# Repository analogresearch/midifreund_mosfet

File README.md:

# midifreund_mosfet

DC IN: 9..28 V 

Ansteuerung durch MIDI note 36 (C2) und eine Oktave dur hoch bis C3.
also:
36 38 40 41 43 45 47 48

MIDI channel und Programm werden binär über DIP Schalter gewählt.

MIDI: Ausnahme DIP Schalter 0000 = MIDI channel 16!

Programme:  
(0) note on schaltet ein, note off schaltet aus.

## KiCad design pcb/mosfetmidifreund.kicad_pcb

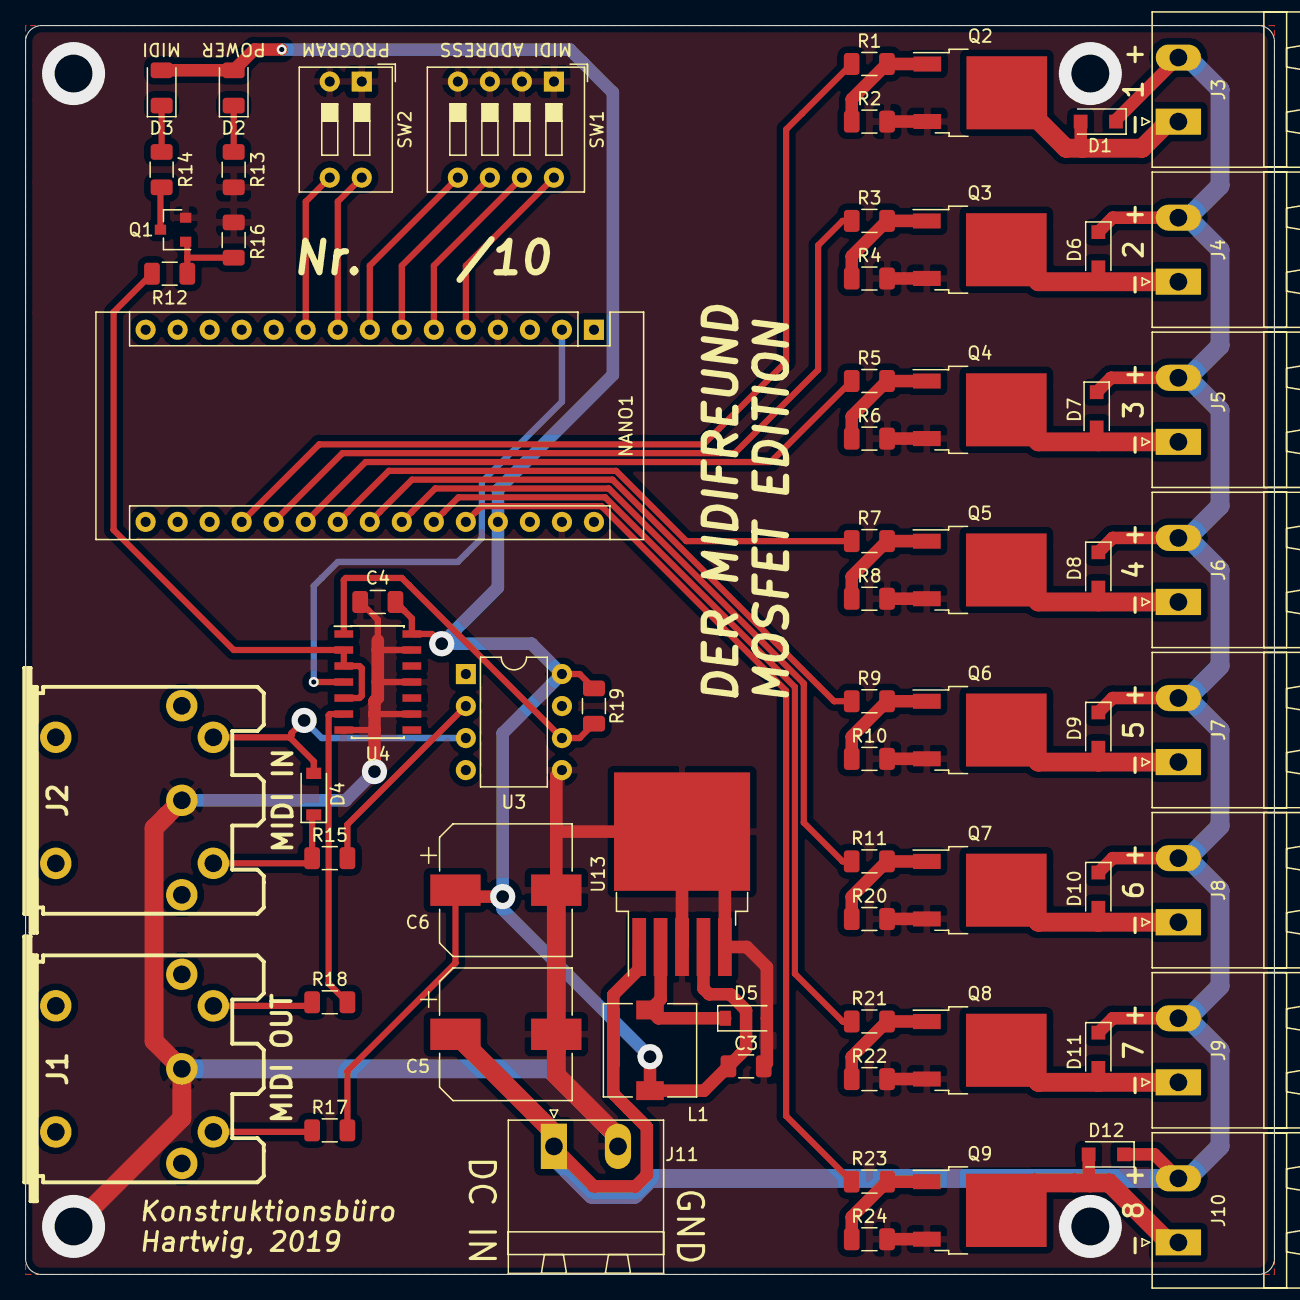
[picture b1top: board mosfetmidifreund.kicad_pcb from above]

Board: 2 copper layers, 99.1 x 99.1 mm, 67 parts (0 on the bottom side), 47 nets.

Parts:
C3, C4: 100n; C_1206_3216Metric
C5, C6: 330uF; CP_Elec_10x10
D1, D6, D7, D8, D9, D10, D11, D12: 1N4001; D_SOD-123F
D2: POWER; LED_1206_3216Metric
D3: MIDI; LED_1206_3216Metric
D4: 1N4148; D_SOD-123
D5: 1N5819; D_SOD-123
J1: MIDI OUT; MIDI_DIN5
J2: MIDI IN; MIDI_DIN5
J3, J4, J5, J6, J7, J8, J9, J10, J11: Conn_01x02; PhoenixContact_MSTBA_2,5_2-G-5,08_1x02_P5.08mm_Horizontal
L1: 330uH; L_7.3x7.3_H3.5
NANO1: Arduino_Nano_v3.x; Arduino_Nano
Q1: BSS138; SOT-23
Q2, Q3, Q4, Q5, Q6, Q7, Q8, Q9: IRLR7843; TO-252-2
R1, R3, R5, R7, R9, R11, R13, R14, R15, R17, R18, R21, R23: 220; R_1206_3216Metric
R2, R4, R6, R8, R10, R20, R22, R24: 10k; R_1206_3216Metric
R12: 470; R_1206_3216Metric
R16: 100k; R_1206_3216Metric
R19: 280; R_1206_3216Metric
SW1: SW_DIP_x04; SW_DIP_SPSTx04_Slide_9.78x12.34mm_W7.62mm_P2.54mm
SW2: SW_DIP_x02; SW_DIP_SPSTx02_Slide_9.78x7.26mm_W7.62mm_P2.54mm
U3: 6N137; DIP-8_W7.62mm
U4: 74LS14; SOIC-14_3.9x8.7mm_P1.27mm
U13: LM2575-5.0BU; TO-263-5_TabPin3

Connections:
+5V: C3.1, C4.1, C6.1, D2.2, D3.2, L1.2, NANO1.27, R17.2, R19.1, U3.8, U4.14, U13.4
GND: C3.2, C4.2, C5.2, C6.2, D5.2, J1.2, J2.2, J11.2, NANO1.4, NANO1.29, Q1.2, Q2.3, Q3.3, Q4.3, Q5.3, Q6.3, Q7.3, Q8.3, Q9.3, R2.2, R4.2, R6.2, R8.2, R10.2, R13.1, R16.2, R20.2, R22.2, R24.2, SW1.1, SW1.2, SW1.3, SW1.4, SW2.1, SW2.2, U3.5, U4.7, U4.9, U4.11, U4.13, U13.3, U13.5
unnamed: D1.2, J3.1, Q2.2
unnamed: D2.1, R13.2
unnamed: D3.1, R14.1
unnamed: D4.1, J2.4, R15.1
unnamed: D4.2, J2.5, U3.3
unnamed: D5.1, L1.1, U13.2
unnamed: D6.2, J4.1, Q3.2
unnamed: D7.2, J5.1, Q4.2
unnamed: D8.2, J6.1, Q5.2
unnamed: D9.2, J7.1, Q6.2
unnamed: D10.2, J8.1, Q7.2
unnamed: D11.2, J9.1, Q8.2
unnamed: D12.2, J10.1, Q9.2
unnamed: J1.4, R17.1
unnamed: J1.5, R18.1
unnamed: NANO1.2, U4.4
unnamed: NANO1.5, SW1.8
unnamed: NANO1.6, SW1.7
unnamed: NANO1.7, SW1.6
unnamed: NANO1.8, SW1.5
unnamed: NANO1.9, SW2.4
unnamed: NANO1.10, SW2.3
unnamed: NANO1.19, R1.1
unnamed: NANO1.20, R3.1
unnamed: NANO1.21, R5.1
unnamed: NANO1.22, R7.1
unnamed: NANO1.23, R9.1
unnamed: NANO1.24, R11.1
unnamed: NANO1.25, R21.1
unnamed: NANO1.26, R23.1
unnamed: Q1.1, R12.2, R16.1
unnamed: Q1.3, R14.2
unnamed: Q2.1, R1.2, R2.1
unnamed: Q3.1, R3.2, R4.1
unnamed: Q4.1, R5.2, R6.1
unnamed: Q5.1, R7.2, R8.1
unnamed: Q6.1, R9.2, R10.1
unnamed: Q7.1, R11.2, R20.1
unnamed: Q8.1, R21.2, R22.1
unnamed: Q9.1, R23.2, R24.1
unnamed: R12.1, U4.2, U4.3, U4.5
unnamed: R15.2, U3.2
unnamed: R18.2, U4.6
unnamed: R19.2, U3.6, U4.1
VDD: C5.1, D1.1, D6.1, D7.1, D8.1, D9.1, D10.1, D11.1, D12.1, J3.2, J4.2, J5.2, J6.2, J7.2, J8.2, J9.2, J10.2, J11.1, U13.1

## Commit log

2019-05-08 foto hinzugefügt
2020-12-02 added pcb layout
